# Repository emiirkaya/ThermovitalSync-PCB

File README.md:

# ThermovitalSync-PCB
 A PCB project with KiCad 8.0 for a vital monitoring and cooling device with GUI
 ## Key features
 + Compact 4-Layer detachable microcontroller PCB with 12V,5V,3.3V power rails from a 11.1 V Lipo battery
 + Pulse, ambient and internal body temperature sensors
 + Peltier and fan modules to implement cooling or heating for the user
 + Microphone and Speaker components to implement
 + GUI with TFT LCD touchscreen using MicroPython 
 + 6x7 cm compact design

Below are the images of the 2 documents from the kicad files of this project
## ThermovitalSync Board schematics 1

## ThermovitalSync Board schematics 2

## Esp32 Custom Microcontroller for ThermovitalSync board schematics 1

## Esp32 Custom Microcontroller for ThermovitalSync board schematics 2

## ThermovitalSync Board 3D Model

## Esp32 Custom Microcontroller for ThermovitalSync board 3D model

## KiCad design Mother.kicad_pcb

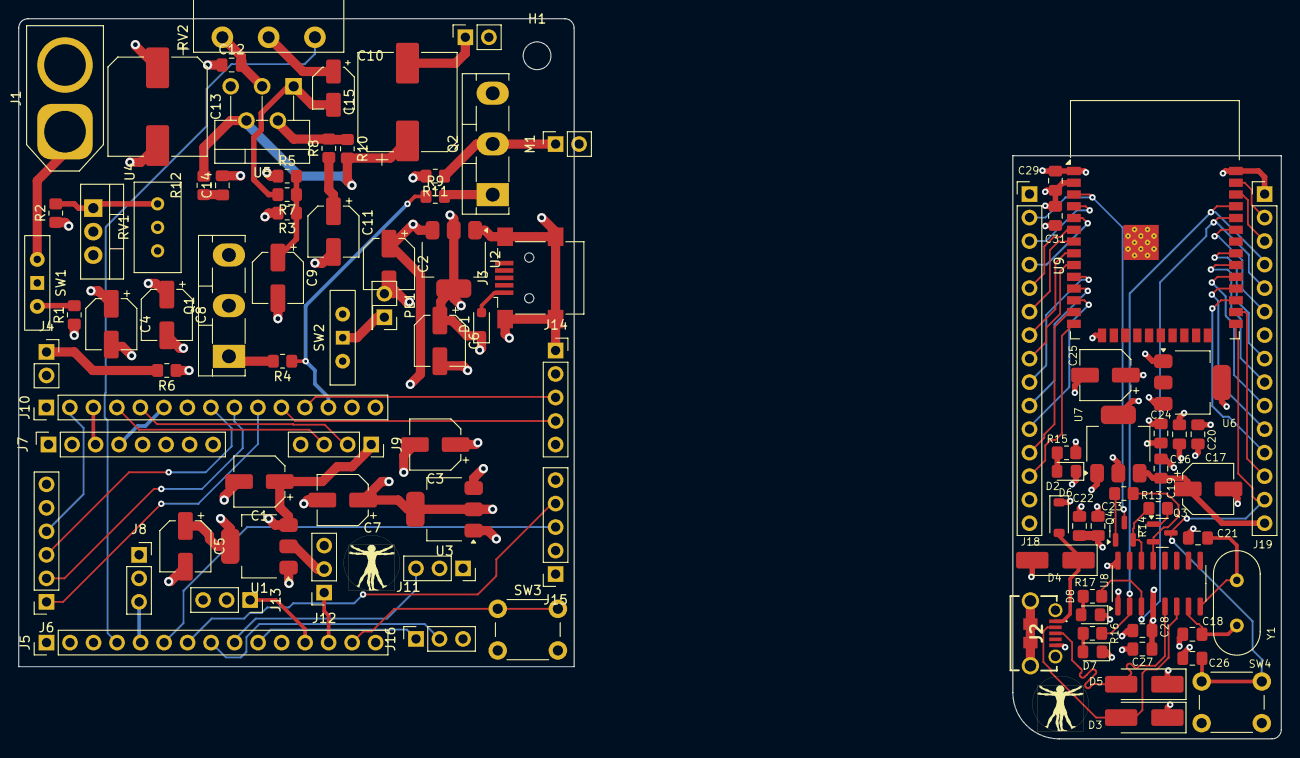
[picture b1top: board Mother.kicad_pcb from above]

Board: 4 copper layers, 136.4 x 77.8 mm, 97 parts (0 on the bottom side), 81 nets.

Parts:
C1, C2, C3, C4: 10uF; CP_Elec_5x5.3
C5, C6, C7, C8, C11: 22uF; CP_Elec_5x5.3
C9, C17, C25: 22u; CP_Elec_5x5.3
C10: 1u; CP_Elec_4x5.3
C12, C23, C26, C27, C31: 0.1u; C_0805_2012Metric_Pad1.18x1.45mm_HandSolder
C13, C15: 1000u; CP_Elec_10x10.5
C14: 0.47u; C_0805_2012Metric_Pad1.18x1.45mm_HandSolder
C16, C20: 10u; C_0805_2012Metric_Pad1.18x1.45mm_HandSolder
C18, C21: 22p; C_0805_2012Metric_Pad1.18x1.45mm_HandSolder
C19, C24: 100n; C_0805_2012Metric_Pad1.18x1.45mm_HandSolder
C22, C28: 4.7u; C_0805_2012Metric_Pad1.18x1.45mm_HandSolder
C29: 22u; C_0805_2012Metric_Pad1.18x1.45mm_HandSolder
D1: BAT60A; D_SOD-323_HandSoldering
D2: RED LED; LED_0805_2012Metric_Pad1.15x1.40mm_HandSolder
D3, D4, D5: SMAJ18CA; D_SMA_Handsoldering
D6: MBR0540; D_SOD-123
D7, D8: LED; LED_0805_2012Metric_Pad1.15x1.40mm_HandSolder
H1: TFT LCD Mount; MountingHole_3mm
J1: xt60; AMASS_XT60-M_1x02_P7.20mm_Vertical
J2: 10118194-0001LF; 101181940001LF
J3: USB_B_Mini; USB_Mini-B_Lumberg_2486_01_Horizontal
J4: Conn_01x02_Pin; PinSocket_1x02_P2.54mm_Vertical
J5: Esp32_2; PinHeader_1x15_P2.54mm_Vertical
J6: Micro_SD; PinSocket_1x06_P2.54mm_Vertical
J7: Gyro; PinSocket_1x08_P2.54mm_Vertical
J8: Pulse; PinSocket_1x03_P2.54mm_Vertical
J9: TFT LCD; PinSocket_1x04_P2.54mm_Vertical
J10: Esp32_1; PinHeader_1x15_P2.54mm_Vertical
J11: INMP441_2; PinSocket_1x03_P2.54mm_Vertical
J12: Ky-015 T-H Sensor; PinSocket_1x03_P2.54mm_Vertical
J13: KY-013 Temp; PinSocket_1x03_P2.54mm_Vertical
J14: JSTICK1; PinSocket_1x05_P2.54mm_Vertical
J15: JSTICK2; PinSocket_1x05_P2.54mm_Vertical
J16: INMP441_1; PinSocket_1x03_P2.54mm_Vertical
J18, J19: Conn_01x15_Pin; PinHeader_1x15_P2.54mm_Vertical
LS1: Speaker; PinSocket_1x02_P2.54mm_Vertical
M1: Fan; PinSocket_1x02_P2.54mm_Vertical
PE1: PeltierElement; PinSocket_2x01_P2.54mm_Vertical
Q1, Q2: TIP142; TO-218-3_Vertical
Q3, Q4: SS8050; SOT-23
R1, R3, R5, R7, R10: 22K; R_0805_2012Metric_Pad1.20x1.40mm_HandSolder
R2: 120; R_0805_2012Metric_Pad1.20x1.40mm_HandSolder
R4, R6, R9, R11: 1.2k; R_0805_2012Metric_Pad1.20x1.40mm_HandSolder
R8: 680R; R_0805_2012Metric_Pad1.20x1.40mm_HandSolder
R12: 2.2R; R_0805_2012Metric_Pad1.20x1.40mm_HandSolder
R13, R14: 10K; R_0805_2012Metric_Pad1.20x1.40mm_HandSolder
R15: 1k2; R_0805_2012Metric_Pad1.20x1.40mm_HandSolder
R16, R17: 330; R_0805_2012Metric_Pad1.20x1.40mm_HandSolder
RV1: 1k trim; Potentiometer_Bourns_3296W_Vertical
RV2: R_Potentiometer; Potentiometer_Piher_PC-16_Single_Horizontal
SW1, SW2: SW_Wuerth_450301014042; SW_Slide-03_Wuerth-WS-SLTV_10x2.5x6.4_P2.54mm
SW3: Reset; SW_PUSH_6mm
SW4: SW_Push; SW_PUSH_6mm
U1, U3, U6: AMS1117-3.3; SOT-223-3_TabPin2
U2, U7: AMS1117-5.0; SOT-223-3_TabPin2
U4: LM350_TO220; TO-220-3_Vertical
U5: TDA2050; TO-220-5_P3.4x3.7mm_StaggerOdd_Lead3.8mm_Vertical
U8: CH340G; SOIC-16_3.9x9.9mm_P1.27mm
U9: ESP32-WROOM-32E; ESP32-WROOM-32D
Y1: Crystal; Crystal_HC49-U_Vertical

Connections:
+3V3: C5.1, C7.1, C20.1, C27.1, C28.2, C29.1, C31.1, J5.15, J6.5, J7.1, J8.2, J11.2, J12.2, J13.2, J16.3, J18.1, U1.2 (VO), U3.2 (VO), U6.2 (VO), U8.4 (V3), U9.2 (VDD)
+5V: C1.1, C6.1, C16.1, C22.1, C23.1, C24.1, C25.1, D1.1 (K), D6.1 (K), J5.1, J9.1, J14.2, J15.2, J18.15, R15.1, U1.3 (VI), U2.2 (VO), U6.3 (VI), U7.2 (VO), U8.16 (VCC)
+5V_BAT: J4.1, R6.2
+12V: C2.1, C3.1, C4.1, C12.1, C13.1, J10.15, R3.2, R11.2, SW1.1 (B), U2.3 (VI), U3.3 (VI), U4.3 (VI), U5.5 (+Vs)
+12V_SW: J1.1, SW1.2 (C)
/4_Pelt: J10.13, R4.1, R9.1
/5_CS: J6.1, J10.10
/14_Vi: J5.4, RV2.1
/16_X: J10.12, J14.3
/17_Y: J10.11, J14.4
/18_SCK: J6.2, J10.9
/19_MOSI: J6.3, J10.8
/21_SDA: J7.4, J10.6
/22_SCL: J7.3, J10.3
/23_MISO: J6.4, J10.2
/25_X: J5.6, J15.3
/26_Y: J5.7, J15.4
/27_Pulse: J5.5, J8.3
/32_SD: J5.9, J11.3
/33_WS: J5.8, J16.2
/35_SCK: J5.10, J16.1
/36_Temp_amb_S: J5.13, J12.1
/39_Temp_body_S: J5.12, J13.1
/EN: J5.14, SW3.1
/Esp32/DTR: Q3.2 (E), R13.1, U8.13 (~DTR)
/Esp32/EN: J18.2, Q4.3 (C), U9.3 (EN)
/Esp32/IO0: C26.2, J19.14, Q3.3 (C), SW4.2, U9.25 (IO0)
/Esp32/IO4: J19.13, U9.26 (IO4)
/Esp32/IO5: J19.10, U9.29 (IO5)
/Esp32/IO12: J18.13, U9.14 (IO12)
/Esp32/IO14: J18.12, U9.13 (IO14)
/Esp32/IO16: J19.12, U9.27 (IO16)
/Esp32/IO17: J19.11, U9.28 (IO17)
/Esp32/IO18: J19.9, U9.30 (IO18)
/Esp32/IO19: J19.8, U9.31 (IO19)
/Esp32/IO21: J19.6, U9.33 (IO21)
/Esp32/IO22: J19.3, U9.36 (IO22)
/Esp32/IO23: J19.2, U9.37 (IO23)
/Esp32/IO25: J18.9, U9.10 (IO25)
/Esp32/IO26: J18.10, U9.11 (IO26)
/Esp32/IO27: J18.11, U9.12 (IO27)
/Esp32/IO32: J18.7, U9.8 (IO32)
/Esp32/IO33: J18.8, U9.9 (IO33)
/Esp32/IO34: J18.5, U9.6 (IO34)
/Esp32/IO35: J18.6, U9.7 (IO35)
/Esp32/RTS: Q4.2 (E), R14.1, U8.14 (~RTS)
/Esp32/RXD: J19.5, R17.1, U8.3 (RXD), U9.34 (RXD0/IO3)
/Esp32/SENSOR_VN: J18.4, U9.5 (SENSOR_VN)
/Esp32/SENSOR_VP: J18.3, U9.4 (SENSOR_VP)
/Esp32/TXD: J19.4, R16.1, U8.2 (TXD), U9.35 (TXD0/IO1)
/Esp32/USB_D+: D5.2 (A2), J2.3, U8.5 (UD+)
/Esp32/USB_D-: D3.2 (A2), J2.2, U8.6 (UD-)
/Esp32/Vbus: D4.1 (A1), D6.2 (A), J2.1
/Esp32/Vin: C17.1, C19.1, J19.15, U7.3 (VI)
/RXD0: J9.2, J10.5
/TXD0: J9.3, J10.4
/V_Fan: M1.1 (+), Q2.2 (C), R11.1
/V_Pelt+: Q1.2 (C), R6.1, SW2.2 (C)
/Vout_?: C8.1, R2.1, U4.2 (VO)
GND: C1.2, C2.2, C3.2, C4.2, C5.2, C6.2, C7.2, C8.2, C9.2, C11.2, C12.2, C13.2, C14.2, C16.2, C17.2, C18.2, C19.2, C20.2, C21.2, C22.2, C23.2, C24.2, C25.2, C26.1, C27.2, C28.1, C29.2, C31.2, D2.1 (K), D3.1 (A1), D4.2 (A2), D5.1 (A1), D7.1 (K), D8.1 (K), J1.2, J2.5, J2.MH1, J2.MH2, J2.MH3, J2.MH4, J2.MP1, J2.MP2, J3.5 (GND), J3.6 (Shield), J4.2, J5.2, J6.6, J7.2, J8.1, J9.4, J10.1, J10.7, J11.1, J12.3, J13.3, J14.1, J15.1, J18.14, J19.1, J19.7, LS1.2, M1.2 (-), PE1.2, Q1.3 (E), Q2.3 (E), R1.1, R5.1, RV1.2, RV1.3, RV2.3, SW2.3 (A), SW3.2, SW4.1, U1.1 (GND), U2.1 (GND), U3.1 (GND), U5.3 (-Vs), U6.1 (GND), U7.1 (GND), U8.1 (GND), U9.1 (GND), U9.15 (GND), U9.38 (GND), U9.39 (GND)
unnamed: C9.1, R3.1, R5.2, R7.1
unnamed: C10.1, RV2.2
unnamed: C11.1, R8.1
unnamed: C14.1, R12.1
unnamed: C15.1, R10.2, R12.2, U5.4
unnamed: C15.2, LS1.1
unnamed: D1.2 (A), J3.1 (VBUS)
unnamed: D2.2 (A), R15.2
unnamed: D7.2 (A), R16.2
unnamed: D8.2 (A), R17.2
unnamed: Q1.1 (B), R4.2
unnamed: Q2.1 (B), R9.2
unnamed: Q3.1 (B), R14.2
unnamed: Q4.1 (B), R13.2
unnamed: R1.2, SW1.3 (A)
unnamed: PE1.1, SW2.1 (B)
unnamed: R2.2, RV1.1, U4.1 (ADJ)
unnamed: C10.2, R7.2, U5.1 (+)
unnamed: R8.2, R10.1, U5.2 (-)
unnamed: C18.1, U8.7 (XI), Y1.1
unnamed: C21.1, U8.8 (XO), Y1.2

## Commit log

2025-05-27 Updated schematics and 3d models
2025-05-27 ThermoVital KiCad files uploaded
